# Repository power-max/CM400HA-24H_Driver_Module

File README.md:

# CM400HA-24H driver
Simple IGBT driver module for Mitubisi IGBT CM400HA-24H modules. This driver module should be capable of switching at up to 100kHz, limited by the SN6505 based DC-DC isolation converter.

The 7741F digital isolator IC is chosen for good CMTI, low propagation delay, high speed, low cost, and the 3 useful return digital channels. 2 standard DIP8 low side driver ICs are used for driving the gate, with 16/20A current capability with the outputs paralelled. In the future I may modify the footprint to allow the use of cheaper SO8 SMD alternative parts as well, or opt for inverting gate drivers and the 7741 (default HIGH state, active low) IC. 

The board features 2 collector voltage feedbacks, one intended for desaturation detection and one for VCC/2 crossover detection to allow output bridge voltage sensing. exact resistor values will need to be determined by the system integrator. There is also feedback for UV lockout with the Pgood return signal. Note: at present there is no fault shutdown, as the active HIGH input to the module directly controls the gate of the IGBT. All shutdown protections should be implemented on an upstream controller.

THE DESIGN IS PROVIDED “AS IS”, WITHOUT WARRANTY OF ANY KIND, EXPRESS OR IMPLIED, INCLUDING BUT NOT LIMITED TO THE WARRANTIES OF MERCHANTABILITY, FITNESS FOR A PARTICULAR PURPOSE AND NONINFRINGEMENT. Refer to the TAPR hardware license for additional detail.

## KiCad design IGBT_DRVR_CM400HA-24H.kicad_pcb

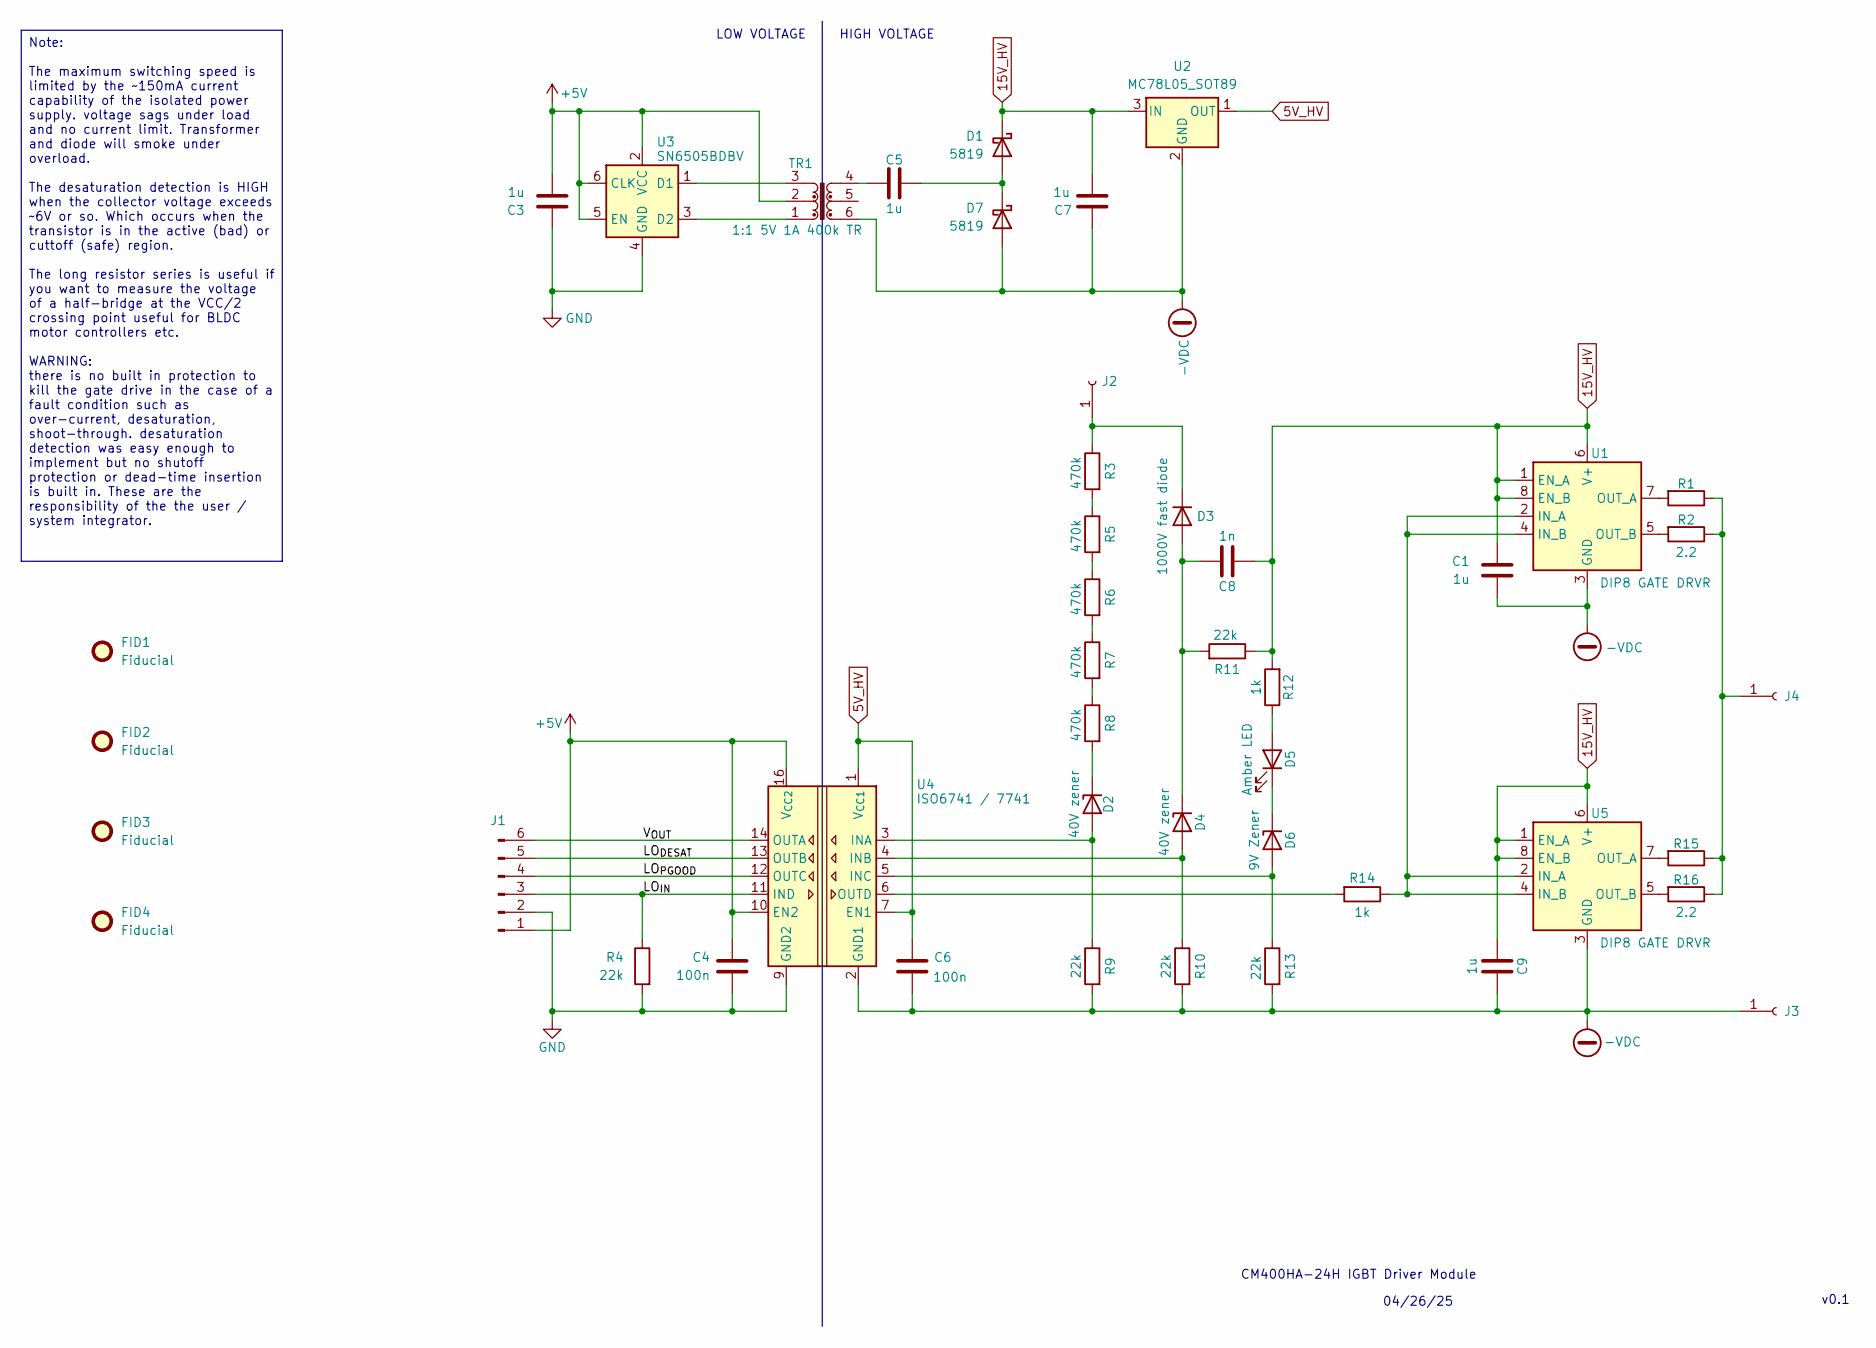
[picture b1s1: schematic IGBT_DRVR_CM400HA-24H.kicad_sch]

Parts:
C1, C3, C5, C7, C9: 1u; C_0603_1608Metric
C4, C6: 100n; C_0603_1608Metric
C8: 1n; C_0603_1608Metric
D1, D7: 5819; D_SOD-123; LCSC C8598
D2, D4: 40V zener; D_SOD-123; LCSC C550214
D3: 1000V fast diode; D_SMA; LCSC C18199160
D5: Amber LED; LED_0603_1608Metric; LCSC C7496818
D6: 9V Zener; D_SOD-123; LCSC C19077407
FID1, FID2, FID3, FID4: Fiducial; Fiducial_1mm_Mask2mm
J1: MSTBA 5.08 terminal block; PhoenixContact_MSTBA_2,5_6-G-5,08_1x06_P5.08mm_Horizontal; LCSC C42378073
J2: direct wire with lug; Pin_D0.7mm_L6.5mm_W1.8mm_FlatFork
J3, J4: hole; MountingHole_4.3mm_M4_Pad_Via
R1, R2, R15, R16: 2.2; R_2512_6332Metric
R3, R5, R6, R7, R8: 470k; R_1206_3216Metric
R4, R9, R10, R11, R13: 22k; R_1206_3216Metric
R12, R14: 1k; R_1206_3216Metric
TR1: 1:1 5V 1A 400k TR; Pulse_PA2004NL; LCSC C42422416
U1, U5: DIP8 GATE DRVR; DIP-8_W7.62mm; LCSC C2874007
U2: MC78L05_SOT89; SOT-89-3; LCSC C42738
U3: SN6505BDBV; SOT-23-6; LCSC C2156022
U4: ISO6741 / 7741; SOIC-16W_7.5x10.3mm_P1.27mm; LCSC C2872241

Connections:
5V_HV: C6.1, U2.1 (OUT), U4.1 (V_{CC1}), U4.7 (EN1)
15V_HV: C1.1, C7.2, C8.1, C9.1, D1.1 (K), R11.1, R12.2, U1.1 (EN_A), U1.6 (V+), U1.8 (EN_B), U2.3 (IN), U5.1 (EN_A), U5.6 (V+), U5.8 (EN_B)
+5V: C3.2, C4.1, J1.1, TR1.2, U3.2 (VCC), U3.5 (EN), U3.6 (CLK), U4.10 (EN2), U4.16 (V_{CC2})
-VDC: C1.2, C6.2, C7.1, C9.2, D7.2 (A), J3.1, R9.2, R10.2, R13.2, TR1.6, U1.3 (GND), U2.2 (GND), U4.2 (GND1), U4.8 (GND1), U5.3 (GND)
/LO_{DESAT}: J1.5, U4.13 (OUTB)
/LO_{IN}: J1.3, R4.1, U4.11 (IND)
/LO_{PGOOD}: J1.4, U4.12 (OUTC)
/V_{OUT}: J1.6, U4.14 (OUTA)
GND: C3.1, C4.2, J1.2, R4.2, U3.4 (GND), U4.9 (GND2), U4.15 (GND2)
unnamed: C5.1, TR1.4
unnamed: C5.2, D1.2 (A), D7.1 (K)
unnamed: D2.2 (A), R9.1, U4.3 (INA)
unnamed: D2.1 (K), R8.2
unnamed: C8.2, D3.2 (A), D4.1 (K), R11.2
unnamed: D3.1 (K), J2.1, R3.1
unnamed: D4.2 (A), R10.1, U4.4 (INB)
unnamed: D5.2 (A), R12.1
unnamed: D5.1 (K), D6.1 (K)
unnamed: D6.2 (A), R13.1, U4.5 (INC)
unnamed: J4.1, R1.1, R2.1, R15.1, R16.1
unnamed: R3.2, R5.1
unnamed: R5.2, R6.1
unnamed: R6.2, R7.1
unnamed: R7.2, R8.1
unnamed: R14.1, U1.2 (IN_A), U1.4 (IN_B), U5.2 (IN_A), U5.4 (IN_B)
unnamed: R1.2, U1.7 (OUT_A)
unnamed: R2.2, U1.5 (OUT_B)
unnamed: TR1.3, U3.1 (D1)
unnamed: TR1.1, U3.3 (D2)
unnamed: R14.2, U4.6 (OUTD)
unnamed: R15.2, U5.7 (OUT_A)
unnamed: R16.2, U5.5 (OUT_B)

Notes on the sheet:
HIGH VOLTAGE
LOW VOLTAGE
CM400HA-24H IGBT Driver Module
04/26/25
v0.1
Note: The maximum switching speed is limited by the ~150mA current capability of the isolated power supply. voltage sags under load and no current limit. Transformer and diode will smoke under overload. The desaturation detection is HIGH when the collector voltage exceeds ~6V or so. Which occurs wh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

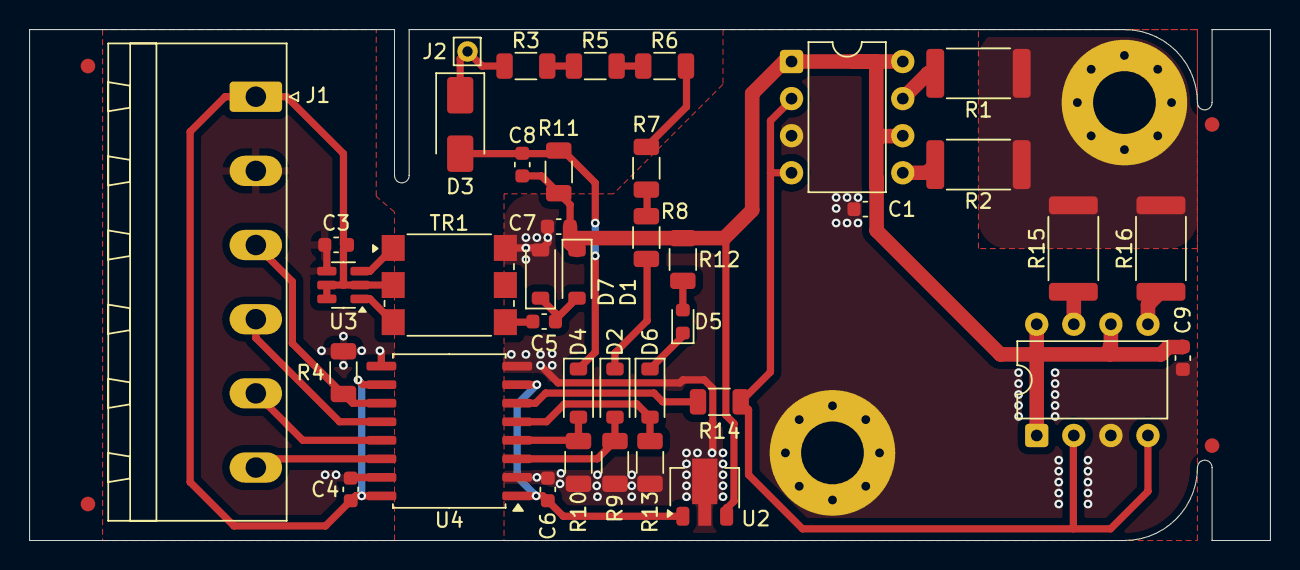
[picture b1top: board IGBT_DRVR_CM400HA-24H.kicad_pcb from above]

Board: 2 copper layers, 85.0 x 35.0 mm, 45 parts (0 on the bottom side), 32 nets.

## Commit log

2025-04-26 initial commit of v0.1
2025-04-26 decided to remove the PCBA files from github as they are generated from the source files and would need to be generated by the user in accordance to their chosen fab house.
2025-04-26 removed reference to now defunct PCBA folder
